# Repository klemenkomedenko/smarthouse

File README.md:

# smarthouse
smart house based on FPGA

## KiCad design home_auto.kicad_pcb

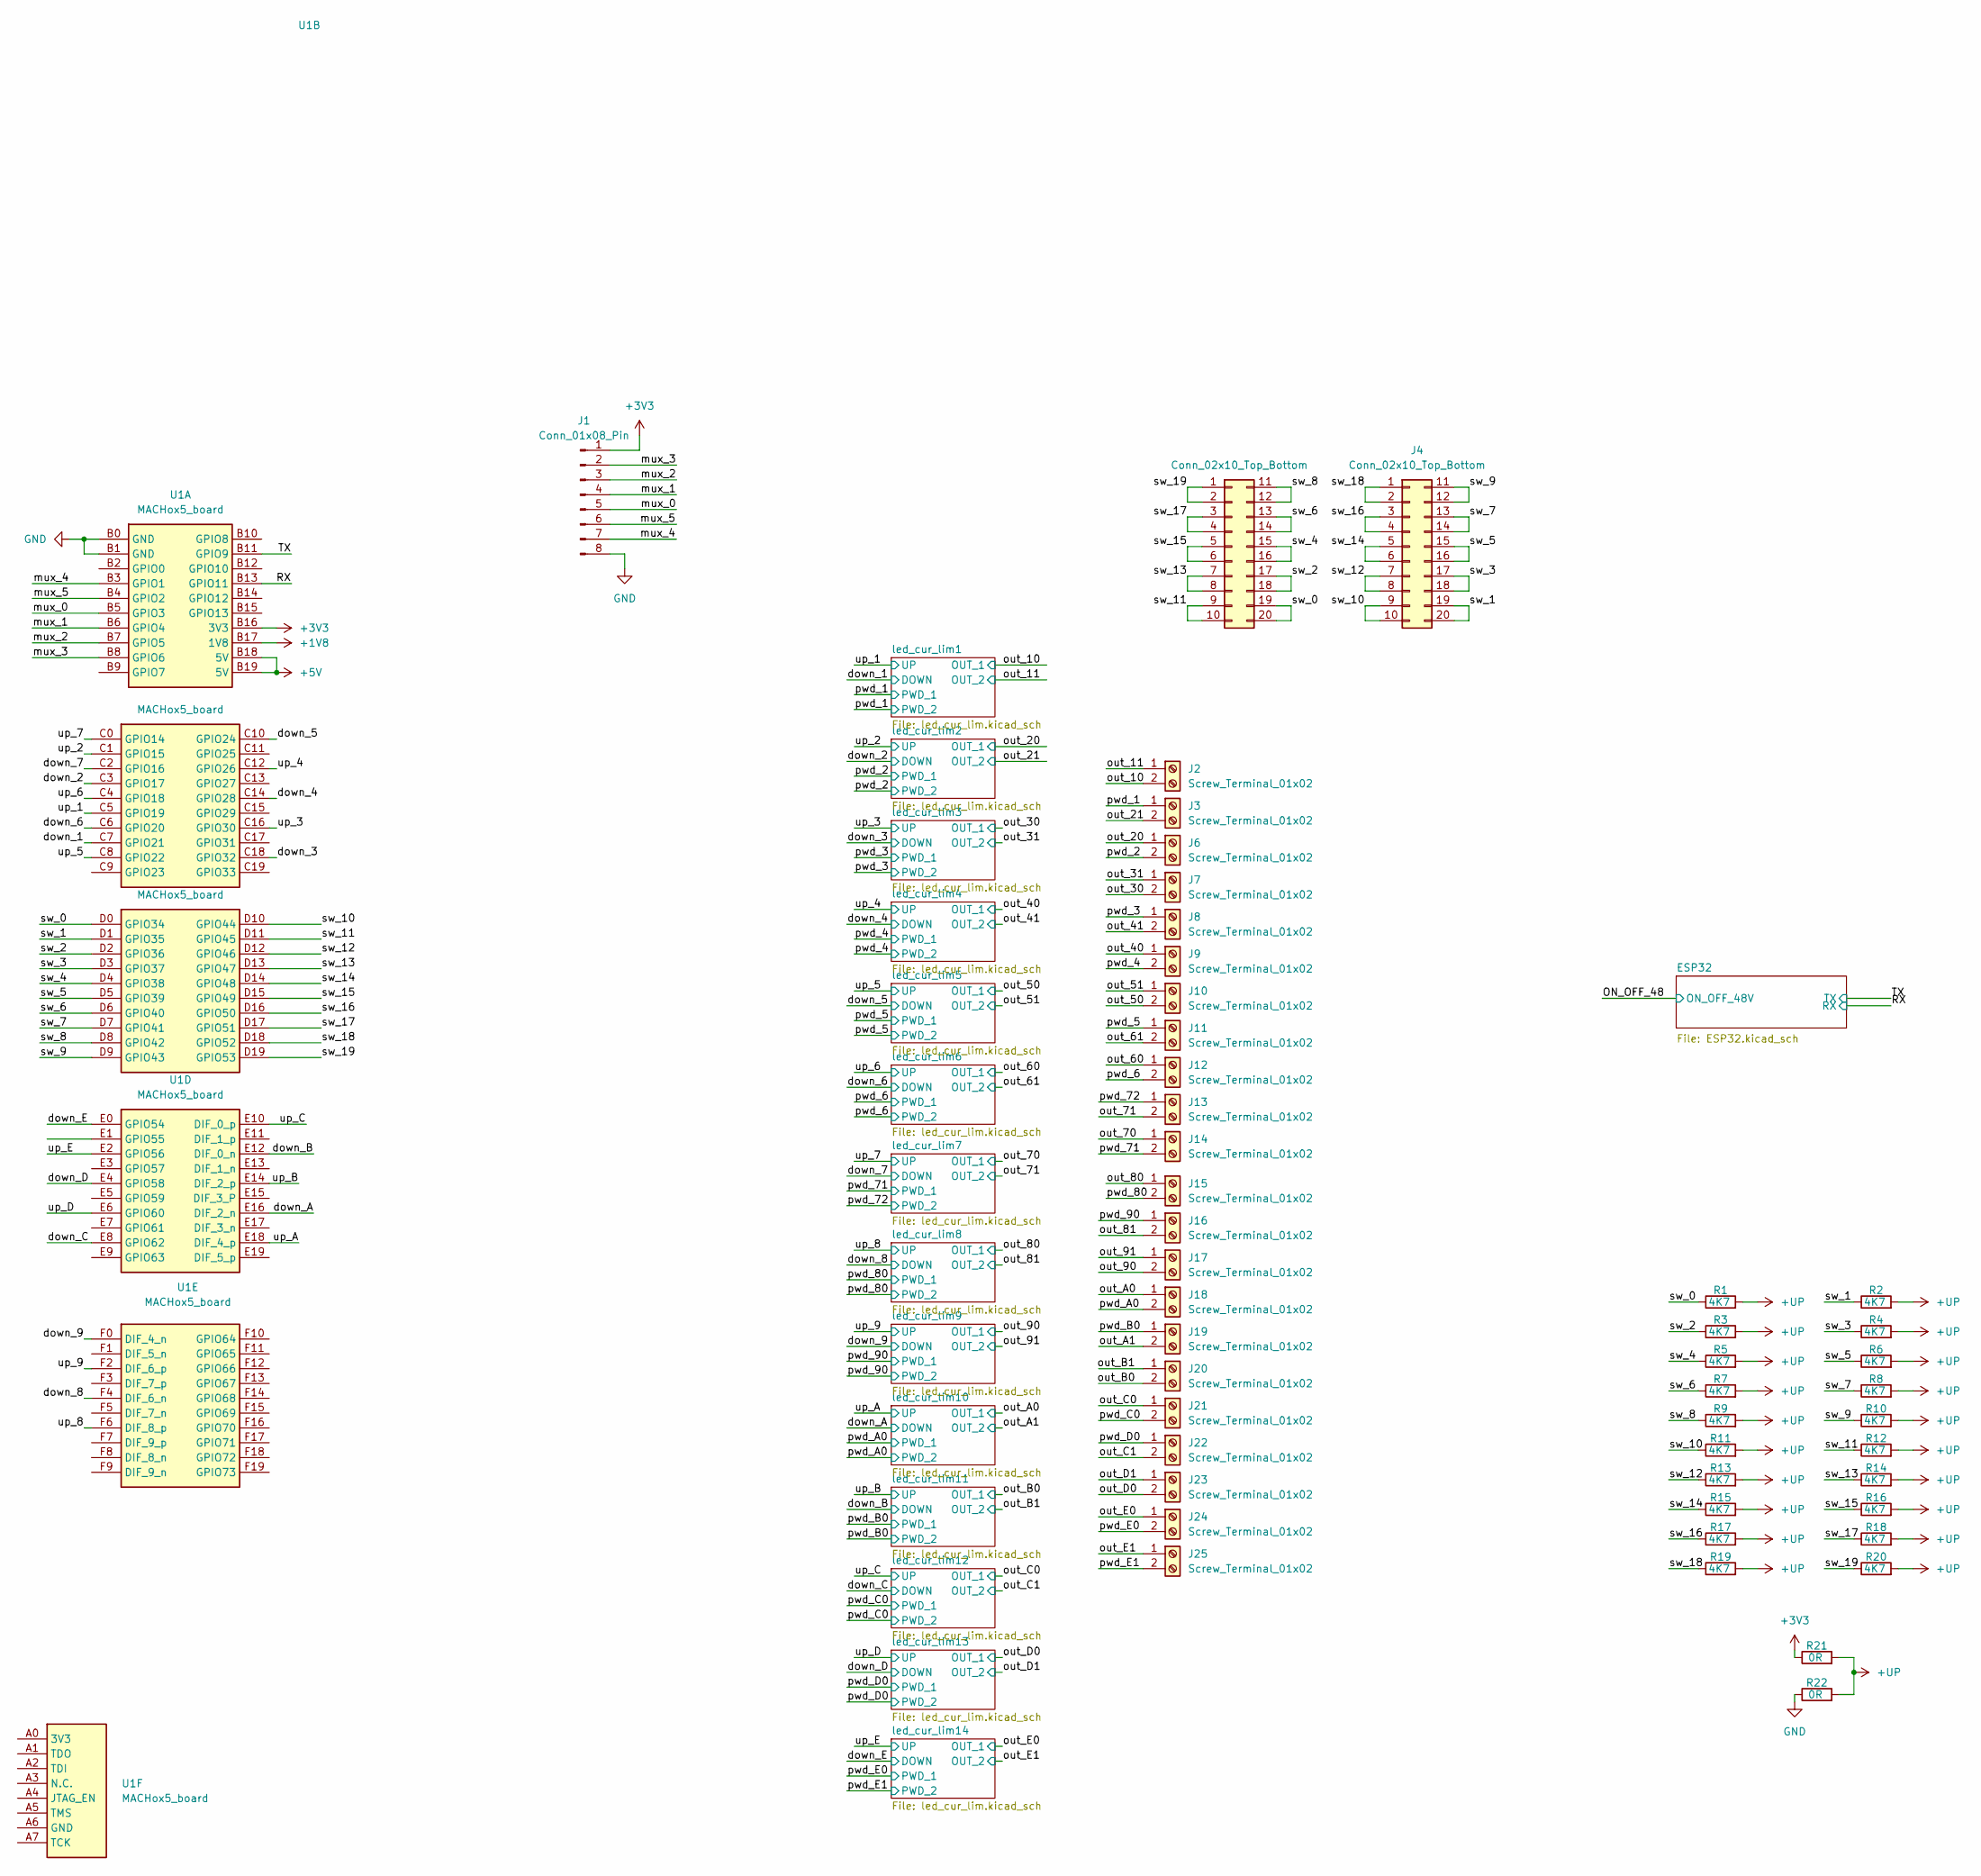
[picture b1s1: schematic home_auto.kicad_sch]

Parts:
J1: Conn_01x08_Pin; PinHeader_1x08_P2.54mm_Vertical
J2, J3, J6, J7, J8, J9, J10, J11, J12, J13, J14, J15, J16, J17, J18, J19, J20, J21, J22, J23, J24, J25: Screw_Terminal_01x02; TC0203620000G
J4, J5: Conn_02x10_Top_Bottom; PinHeader_2x10_P2.54mm_Vertical_SMD
R1, R2, R3, R4, R5, R6, R7, R8, R9, R10, R11, R12, R13, R14, R15, R16, R17, R18, R19, R20: 4K7; R_0603_1608Metric
R21: 0R; R_0805_2012Metric
R22: 0R; R_0603_1608Metric
U1: MACHox5_board; machox5_board

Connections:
+1V8: U1.B17 (1V8)
+3V3: J1.1, R21.1, U1.B16 (3V3); also elsewhere on the board
+5V: U1.B18 (5V), U1.B19 (5V); also elsewhere on the board
+UP: R1.2, R2.2, R3.2, R4.2, R5.2, R6.2, R7.2, R8.2, R9.2, R10.2, R11.2, R12.2, R13.2, R14.2, R15.2, R16.2, R17.2, R18.2, R19.2, R20.2, R21.2, R22.2
/RX: U1.B13 (GPIO11); also elsewhere on the board
/TX: U1.B11 (GPIO9); also elsewhere on the board
/down_1: U1.C7 (GPIO21); also elsewhere on the board
/down_2: U1.C3 (GPIO17); also elsewhere on the board
/down_3: U1.C18 (GPIO32); also elsewhere on the board
/down_4: U1.C14 (GPIO28); also elsewhere on the board
/down_5: U1.C10 (GPIO24); also elsewhere on the board
/down_6: U1.C6 (GPIO20); also elsewhere on the board
/down_7: U1.C2 (GPIO16); also elsewhere on the board
/down_8: U1.F4 (DIF_6_n); also elsewhere on the board
/down_9: U1.F0 (DIF_4_n); also elsewhere on the board
/down_A: U1.E16 (DIF_2_n); also elsewhere on the board
/down_B: U1.E12 (DIF_0_n); also elsewhere on the board
/down_C: U1.E8 (GPIO62); also elsewhere on the board
/down_D: U1.E4 (GPIO58); also elsewhere on the board
/down_E: U1.E0 (GPIO54); also elsewhere on the board
/mux_0: J1.5, U1.B5 (GPIO3)
/mux_1: J1.4, U1.B6 (GPIO4)
/mux_2: J1.3, U1.B7 (GPIO5)
/mux_3: J1.2, U1.B8 (GPIO6)
/mux_4: J1.7, U1.B3 (GPIO1)
/mux_5: J1.6, U1.B4 (GPIO2)
/out_10: J2.2; also elsewhere on the board
/out_11: J2.1; also elsewhere on the board
/out_20: J6.1; also elsewhere on the board
/out_21: J3.2; also elsewhere on the board
/out_30: J7.2; also elsewhere on the board
/out_31: J7.1; also elsewhere on the board
/out_40: J9.1; also elsewhere on the board
/out_41: J8.2; also elsewhere on the board
/out_50: J10.2; also elsewhere on the board
/out_51: J10.1; also elsewhere on the board
/out_60: J12.1; also elsewhere on the board
/out_61: J11.2; also elsewhere on the board
/out_70: J14.1; also elsewhere on the board
/out_71: J13.2; also elsewhere on the board
/out_80: J15.1; also elsewhere on the board
/out_81: J16.2; also elsewhere on the board
/out_90: J17.2; also elsewhere on the board
/out_91: J17.1; also elsewhere on the board
/out_A0: J18.1; also elsewhere on the board
/out_A1: J19.2; also elsewhere on the board
/out_B0: J20.2; also elsewhere on the board
/out_B1: J20.1; also elsewhere on the board
/out_C0: J21.1; also elsewhere on the board
/out_C1: J22.2; also elsewhere on the board
/out_D0: J23.2; also elsewhere on the board
/out_D1: J23.1; also elsewhere on the board
/out_E0: J24.1; also elsewhere on the board
/out_E1: J25.1; also elsewhere on the board
/pwd_1: J3.1; also elsewhere on the board
/pwd_2: J6.2; also elsewhere on the board
/pwd_3: J8.1; also elsewhere on the board
/pwd_4: J9.2; also elsewhere on the board
/pwd_5: J11.1; also elsewhere on the board
/pwd_6: J12.2; also elsewhere on the board
/pwd_71: J14.2; also elsewhere on the board
/pwd_72: J13.1; also elsewhere on the board
/pwd_80: J15.2; also elsewhere on the board
/pwd_90: J16.1; also elsewhere on the board
/pwd_A0: J18.2; also elsewhere on the board
/pwd_B0: J19.1; also elsewhere on the board
/pwd_C0: J21.2; also elsewhere on the board
/pwd_D0: J22.1; also elsewhere on the board
/pwd_E0: J24.2; also elsewhere on the board
/pwd_E1: J25.2; also elsewhere on the board
/sw_0: J5.19, J5.20, R1.1, U1.D0 (GPIO34)
/sw_1: J4.19, J4.20, R2.1, U1.D1 (GPIO35)
/sw_2: J5.17, J5.18, R3.1, U1.D2 (GPIO36)
/sw_3: J4.17, J4.18, R4.1, U1.D3 (GPIO37)
/sw_4: J5.15, J5.16, R5.1, U1.D4 (GPIO38)
/sw_5: J4.15, J4.16, R6.1, U1.D5 (GPIO39)
/sw_6: J5.13, J5.14, R7.1, U1.D6 (GPIO40)
/sw_7: J4.13, J4.14, R8.1, U1.D7 (GPIO41)
/sw_8: J5.11, J5.12, R9.1, U1.D8 (GPIO42)
/sw_9: J4.11, J4.12, R10.1, U1.D9 (GPIO43)
/sw_10: J4.9, J4.10, R11.1, U1.D10 (GPIO44)
/sw_11: J5.9, J5.10, R12.1, U1.D11 (GPIO45)
/sw_12: J4.7, J4.8, R13.1, U1.D12 (GPIO46)
/sw_13: J5.7, J5.8, R14.1, U1.D13 (GPIO47)
/sw_14: J4.5, J4.6, R15.1, U1.D14 (GPIO48)
/sw_15: J5.5, J5.6, R16.1, U1.D15 (GPIO49)
/sw_16: J4.3, J4.4, R17.1, U1.D16 (GPIO50)
/sw_17: J5.3, J5.4, R18.1, U1.D17 (GPIO51)
/sw_18: J4.1, J4.2, R19.1, U1.D18 (GPIO52)
/sw_19: J5.1, J5.2, R20.1, U1.D19 (GPIO53)
/up_1: U1.C5 (GPIO19); also elsewhere on the board
/up_2: U1.C1 (GPIO15); also elsewhere on the board
/up_3: U1.C16 (GPIO30); also elsewhere on the board
/up_4: U1.C12 (GPIO26); also elsewhere on the board
/up_5: U1.C8 (GPIO22); also elsewhere on the board
/up_6: U1.C4 (GPIO18); also elsewhere on the board
/up_7: U1.C0 (GPIO14); also elsewhere on the board
/up_8: U1.F6 (DIF_8_p); also elsewhere on the board
/up_9: U1.F2 (DIF_6_p); also elsewhere on the board
/up_A: U1.E18 (DIF_4_p); also elsewhere on the board
/up_B: U1.E14 (DIF_2_p); also elsewhere on the board
/up_C: U1.E10 (DIF_0_p); also elsewhere on the board
/up_D: U1.E6 (GPIO60); also elsewhere on the board
/up_E: U1.E2 (GPIO56); also elsewhere on the board
GND: J1.8, R22.1, U1.B0 (GND), U1.B1 (GND); also elsewhere on the board

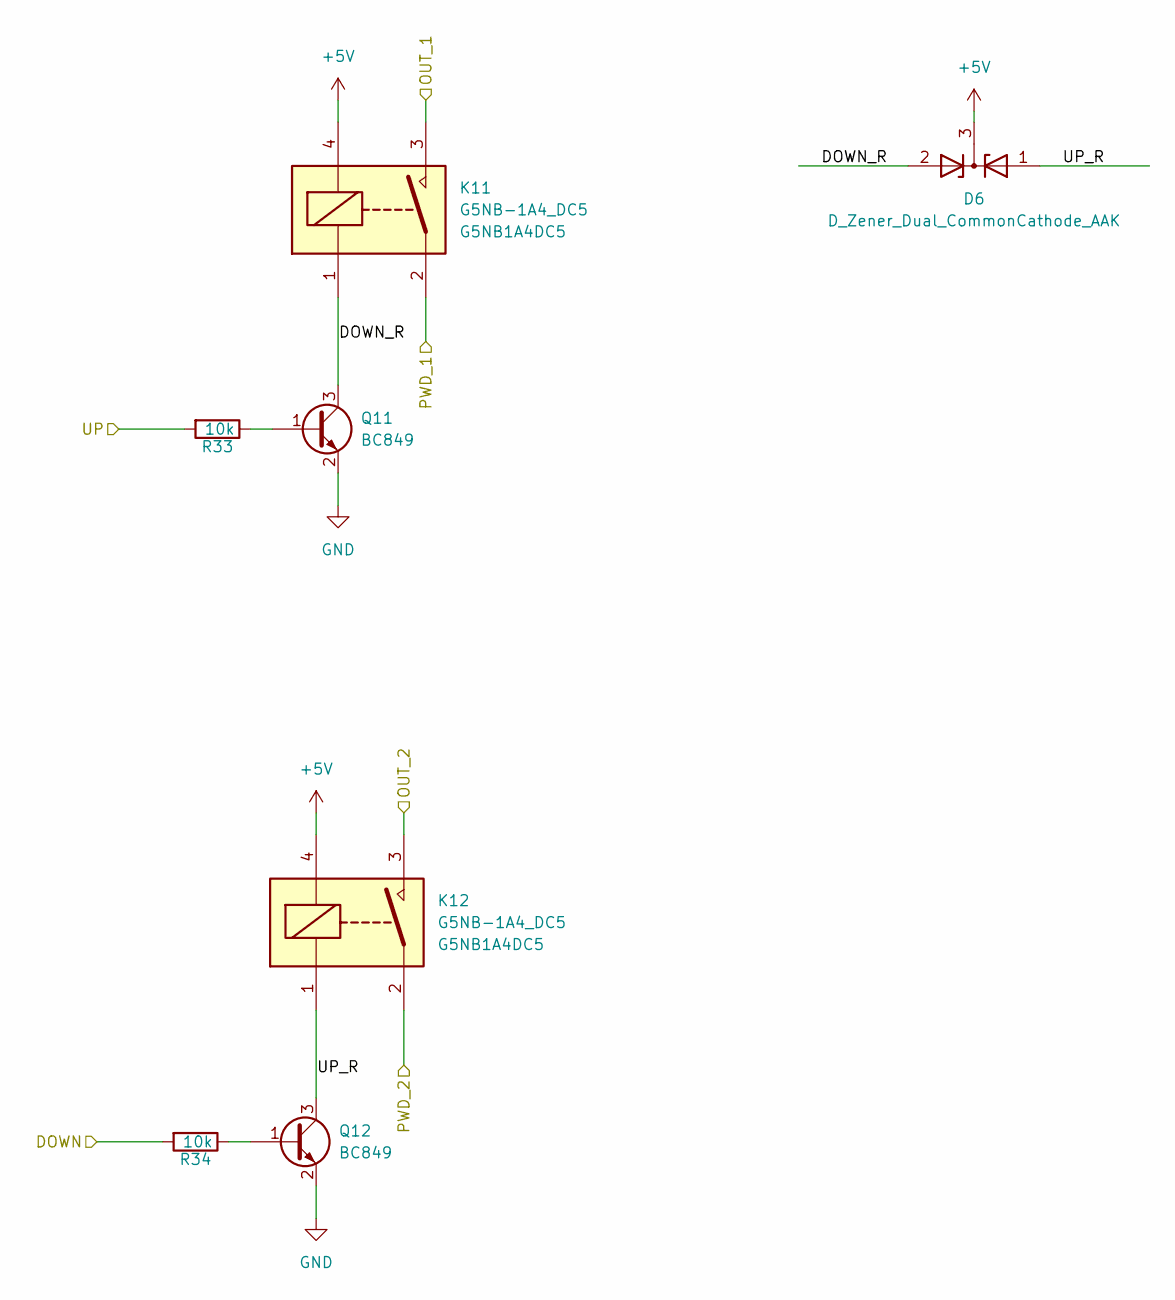
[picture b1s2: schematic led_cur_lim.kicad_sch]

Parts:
D6: D_Zener_Dual_CommonCathode_AAK; SOT-23
K11, K12: G5NB-1A4_DC5; G5NB1A4DC5; Mouser Part Number 653-G5NB-1A4DC5
Q11, Q12: BC849; SOT-23
R33, R34: 10k; R_0603_1608Metric

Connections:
+5V: D6.3 (K), K11.4, K12.4; also elsewhere on the board
/down_1: R34.2; also elsewhere on the board
/led_cur_lim1/DOWN_R: D6.2 (A), K11.1, Q11.3 (C)
/led_cur_lim1/UP_R: D6.1 (A), K12.1, Q12.3 (C)
/out_10: K11.3; also elsewhere on the board
/out_11: K12.3; also elsewhere on the board
/pwd_1: K11.2, K12.2; also elsewhere on the board
/up_1: R33.2; also elsewhere on the board
GND: Q11.2 (E), Q12.2 (E); also elsewhere on the board
unnamed: Q11.1 (B), R33.1
unnamed: Q12.1 (B), R34.1

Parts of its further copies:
D1, D2, D3, D4, D5, D7, D8, D9, D10, D11, D12, D13, D14: D_Zener_Dual_CommonCathode_AAK; SOT-23
K1, K2, K3, K4, K5, K6, K7, K8, K9, K10, K13, K14, K15, K16, K17, K18, K19, K20, K21, K22, K23, K24, K25, K26, K27, K28: G5NB-1A4_DC5; G5NB1A4DC5; Mouser Part Number 653-G5NB-1A4DC5
Q1, Q2, Q3, Q4, Q5, Q6, Q7, Q8, Q9, Q10, Q13, Q14, Q15, Q16, Q17, Q18, Q19, Q20, Q21, Q22, Q23, Q24, Q25, Q26, Q27, Q28: BC849; SOT-23
R23, R24, R25, R26, R27, R28, R29, R30, R31, R32, R35, R36, R37, R38, R39, R40, R41, R42, R43, R44, R45, R46, R47, R48, R49, R50: 10k; R_0603_1608Metric

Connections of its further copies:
+5V: D1.3 (K), D2.3 (K), D3.3 (K), D4.3 (K), D5.3 (K), D7.3 (K), D8.3 (K), D9.3 (K), D10.3 (K), D11.3 (K), D12.3 (K), D13.3 (K), D14.3 (K), K1.4, K2.4, K3.4, K4.4, K5.4, K6.4, K7.4, K8.4, K9.4, K10.4, K13.4, K14.4, K15.4, K16.4, K17.4, K18.4, K19.4, K20.4, K21.4, K22.4, K23.4, K24.4, K25.4, K26.4, K27.4, K28.4; also elsewhere on the board
/down_2: R24.2; also elsewhere on the board
/down_3: R26.2; also elsewhere on the board
/down_4: R28.2; also elsewhere on the board
/down_5: R30.2; also elsewhere on the board
/down_6: R32.2; also elsewhere on the board
/down_7: R36.2; also elsewhere on the board
/down_8: R38.2; also elsewhere on the board
/down_9: R40.2; also elsewhere on the board
/down_A: R42.2; also elsewhere on the board
/down_B: R44.2; also elsewhere on the board
/down_C: R46.2; also elsewhere on the board
/down_D: R48.2; also elsewhere on the board
/down_E: R50.2; also elsewhere on the board
/led_cur_lim2/DOWN_R: D1.2 (A), K1.1, Q1.3 (C)
/led_cur_lim2/UP_R: D1.1 (A), K2.1, Q2.3 (C)
/led_cur_lim3/DOWN_R: D2.2 (A), K3.1, Q3.3 (C)
/led_cur_lim3/UP_R: D2.1 (A), K4.1, Q4.3 (C)
/led_cur_lim4/DOWN_R: D3.2 (A), K5.1, Q5.3 (C)
/led_cur_lim4/UP_R: D3.1 (A), K6.1, Q6.3 (C)
/led_cur_lim5/DOWN_R: D4.2 (A), K7.1, Q7.3 (C)
/led_cur_lim5/UP_R: D4.1 (A), K8.1, Q8.3 (C)
/led_cur_lim6/DOWN_R: D5.2 (A), K9.1, Q9.3 (C)
/led_cur_lim6/UP_R: D5.1 (A), K10.1, Q10.3 (C)
/led_cur_lim7/DOWN_R: D7.2 (A), K13.1, Q13.3 (C)
/led_cur_lim7/UP_R: D7.1 (A), K14.1, Q14.3 (C)
/led_cur_lim8/DOWN_R: D8.2 (A), K15.1, Q15.3 (C)
/led_cur_lim8/UP_R: D8.1 (A), K16.1, Q16.3 (C)
/led_cur_lim9/DOWN_R: D9.2 (A), K17.1, Q17.3 (C)
/led_cur_lim9/UP_R: D9.1 (A), K18.1, Q18.3 (C)
/led_cur_lim10/DOWN_R: D10.2 (A), K19.1, Q19.3 (C)
/led_cur_lim10/UP_R: D10.1 (A), K20.1, Q20.3 (C)
/led_cur_lim11/DOWN_R: D11.2 (A), K21.1, Q21.3 (C)
/led_cur_lim11/UP_R: D11.1 (A), K22.1, Q22.3 (C)
/led_cur_lim12/DOWN_R: D12.2 (A), K23.1, Q23.3 (C)
/led_cur_lim12/UP_R: D12.1 (A), K24.1, Q24.3 (C)
/led_cur_lim13/DOWN_R: D13.2 (A), K25.1, Q25.3 (C)
/led_cur_lim13/UP_R: D13.1 (A), K26.1, Q26.3 (C)
/led_cur_lim14/DOWN_R: D14.2 (A), K27.1, Q27.3 (C)
/led_cur_lim14/UP_R: D14.1 (A), K28.1, Q28.3 (C)
/out_20: K1.3; also elsewhere on the board
/out_21: K2.3; also elsewhere on the board
/out_30: K3.3; also elsewhere on the board
/out_31: K4.3; also elsewhere on the board
/out_40: K5.3; also elsewhere on the board
/out_41: K6.3; also elsewhere on the board
/out_50: K7.3; also elsewhere on the board
/out_51: K8.3; also elsewhere on the board
/out_60: K9.3; also elsewhere on the board
/out_61: K10.3; also elsewhere on the board
/out_70: K13.3; also elsewhere on the board
/out_71: K14.3; also elsewhere on the board
/out_80: K15.3; also elsewhere on the board
/out_81: K16.3; also elsewhere on the board
/out_90: K17.3; also elsewhere on the board
/out_91: K18.3; also elsewhere on the board
/out_A0: K19.3; also elsewhere on the board
/out_A1: K20.3; also elsewhere on the board
/out_B0: K21.3; also elsewhere on the board
/out_B1: K22.3; also elsewhere on the board
/out_C0: K23.3; also elsewhere on the board
/out_C1: K24.3; also elsewhere on the board
/out_D0: K25.3; also elsewhere on the board
/out_D1: K26.3; also elsewhere on the board
/out_E0: K27.3; also elsewhere on the board
/out_E1: K28.3; also elsewhere on the board
/pwd_2: K1.2, K2.2; also elsewhere on the board
/pwd_3: K3.2, K4.2; also elsewhere on the board
/pwd_4: K5.2, K6.2; also elsewhere on the board
/pwd_5: K7.2, K8.2; also elsewhere on the board
/pwd_6: K9.2, K10.2; also elsewhere on the board
/pwd_71: K13.2; also elsewhere on the board
/pwd_72: K14.2; also elsewhere on the board
/pwd_80: K15.2, K16.2; also elsewhere on the board
/pwd_90: K17.2, K18.2; also elsewhere on the board
/pwd_A0: K19.2, K20.2; also elsewhere on the board
/pwd_B0: K21.2, K22.2; also elsewhere on the board
/pwd_C0: K23.2, K24.2; also elsewhere on the board
/pwd_D0: K25.2, K26.2; also elsewhere on the board
/pwd_E0: K27.2; also elsewhere on the board
/pwd_E1: K28.2; also elsewhere on the board
/up_2: R23.2; also elsewhere on the board
/up_3: R25.2; also elsewhere on the board
/up_4: R27.2; also elsewhere on the board
/up_5: R29.2; also elsewhere on the board
/up_6: R31.2; also elsewhere on the board
/up_7: R35.2; also elsewhere on the board
/up_8: R37.2; also elsewhere on the board
/up_9: R39.2; also elsewhere on the board
/up_A: R41.2; also elsewhere on the board
/up_B: R43.2; also elsewhere on the board
/up_C: R45.2; also elsewhere on the board
/up_D: R47.2; also elsewhere on the board
/up_E: R49.2; also elsewhere on the board
GND: Q1.2 (E), Q2.2 (E), Q3.2 (E), Q4.2 (E), Q5.2 (E), Q6.2 (E), Q7.2 (E), Q8.2 (E), Q9.2 (E), Q10.2 (E), Q13.2 (E), Q14.2 (E), Q15.2 (E), Q16.2 (E), Q17.2 (E), Q18.2 (E), Q19.2 (E), Q20.2 (E), Q21.2 (E), Q22.2 (E), Q23.2 (E), Q24.2 (E), Q25.2 (E), Q26.2 (E), Q27.2 (E), Q28.2 (E); also elsewhere on the board
unnamed: Q1.1 (B), R23.1
unnamed: Q2.1 (B), R24.1
unnamed: Q3.1 (B), R25.1
unnamed: Q4.1 (B), R26.1
unnamed: Q5.1 (B), R27.1
unnamed: Q6.1 (B), R28.1
unnamed: Q7.1 (B), R29.1
unnamed: Q8.1 (B), R30.1
unnamed: Q9.1 (B), R31.1
unnamed: Q10.1 (B), R32.1
unnamed: Q13.1 (B), R35.1
unnamed: Q14.1 (B), R36.1
unnamed: Q15.1 (B), R37.1
unnamed: Q16.1 (B), R38.1
unnamed: Q17.1 (B), R39.1
unnamed: Q18.1 (B), R40.1
unnamed: Q19.1 (B), R41.1
unnamed: Q20.1 (B), R42.1
unnamed: Q21.1 (B), R43.1
unnamed: Q22.1 (B), R44.1
unnamed: Q23.1 (B), R45.1
unnamed: Q24.1 (B), R46.1
unnamed: Q25.1 (B), R47.1
unnamed: Q26.1 (B), R48.1
unnamed: Q27.1 (B), R49.1
unnamed: Q28.1 (B), R50.1

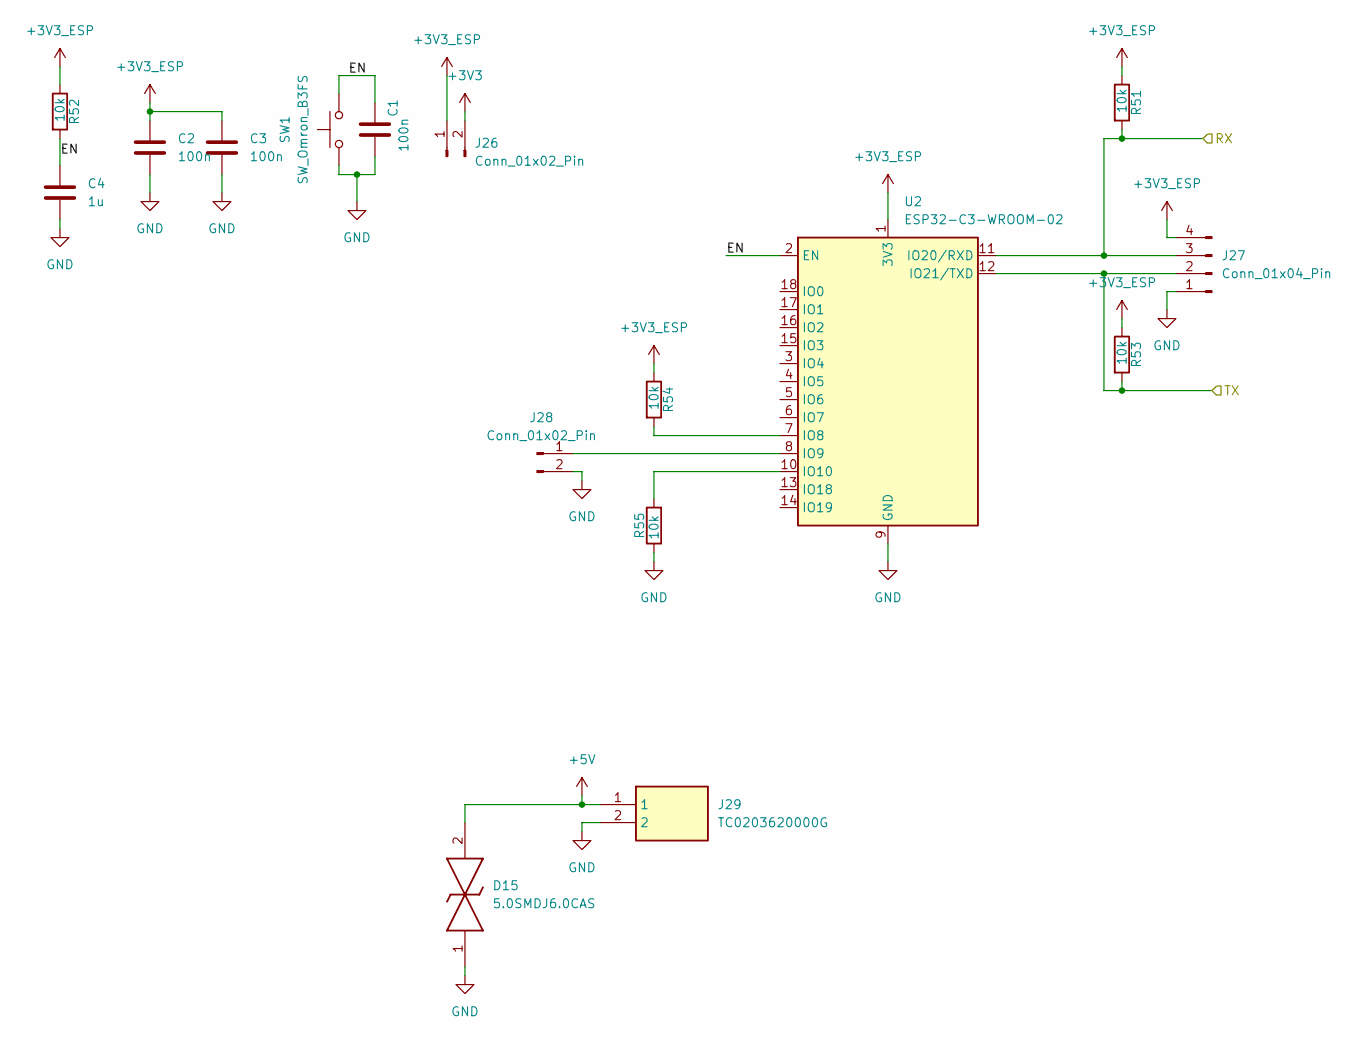
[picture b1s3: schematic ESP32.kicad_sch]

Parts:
C1, C2, C3: 100n; C_0603_1608Metric
C4: 1u; C_0603_1608Metric
D15: 5.0SMDJ6.0CAS; DIONM7959X262N; Mouser Part Number 576-5.0SMDJ6.0CAS
J26, J28: Conn_01x02_Pin; PinHeader_1x02_P1.27mm_Vertical
J27: Conn_01x04_Pin; PinHeader_1x04_P2.54mm_Vertical
J29: TC0203620000G; Mouser Part Number 649-TC02036200J0G
R51, R52, R53, R54, R55: 10k; R_0603_1608Metric
SW1: SW_Omron_B3FS; SW_SPST_Omron_B3FS-105xP
U2: ESP32-C3-WROOM-02

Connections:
+3V3: J26.2; also elsewhere on the board
+3V3_ESP: C2.1, C3.1, J26.1, J27.4, R51.1, R52.1, R53.1, R54.1, U2.1 (3V3)
+5V: D15.2, J29.1; also elsewhere on the board
/ESP32/EN: C1.1, C4.1, R52.2, SW1.2, U2.2 (EN)
/RX: J27.3, R51.2, U2.11 (IO20/RXD); also elsewhere on the board
/TX: J27.2, R53.2, U2.12 (IO21/TXD); also elsewhere on the board
GND: C1.2, C2.2, C3.2, C4.2, D15.1, J27.1, J28.2, J29.2, R55.1, SW1.1, U2.9 (GND), U2.19 (GND); also elsewhere on the board
unnamed: J28.1, U2.8 (IO9)
unnamed: R54.2, U2.7 (IO8)
unnamed: R55.2, U2.10 (IO10)

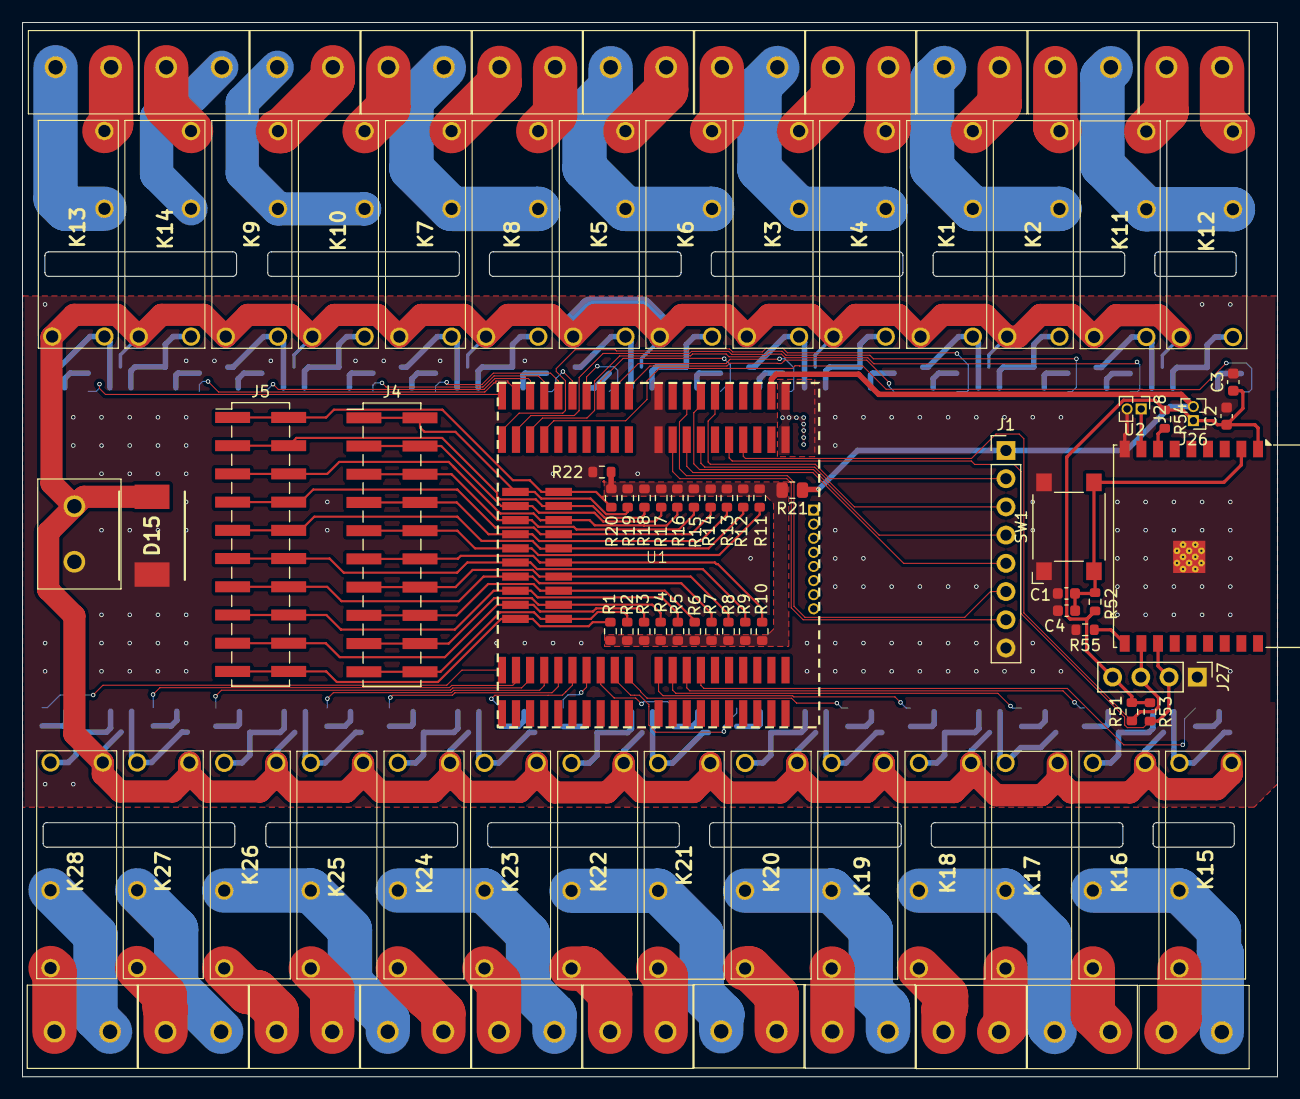
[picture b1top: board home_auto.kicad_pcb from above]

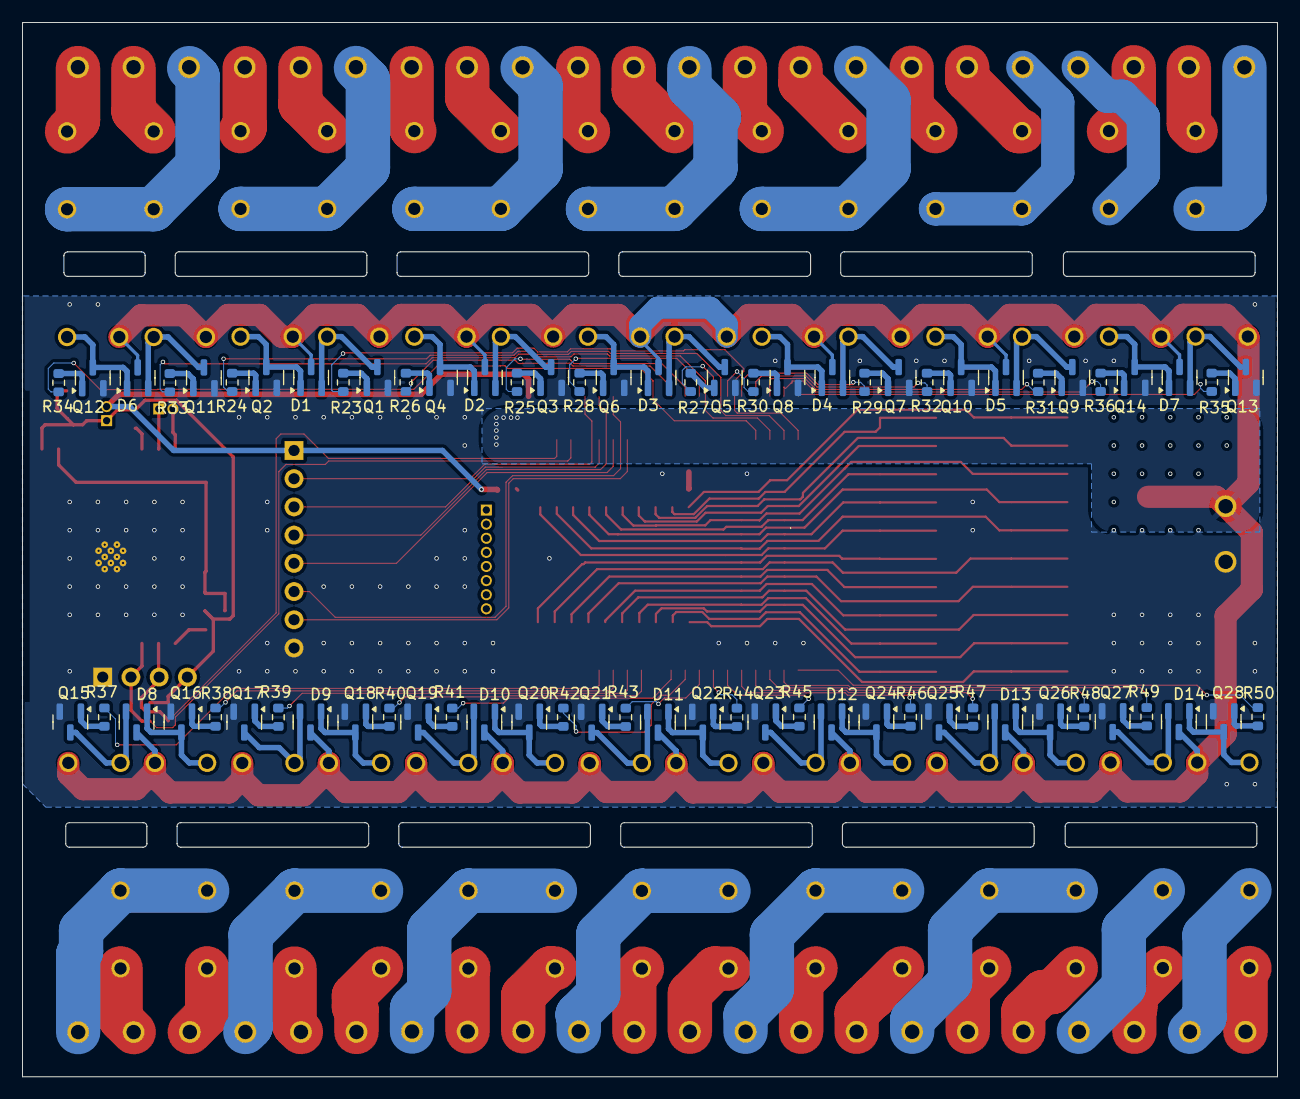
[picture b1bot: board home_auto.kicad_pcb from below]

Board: 2 copper layers, 113.0 x 94.9 mm, 162 parts (70 on the bottom side), 165 nets.

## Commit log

2024-11-05 board with normal header pins
2024-11-05 relay unit
2024-11-06 relay placment
2024-11-10 filse fo JCL pcb generated
2024-11-10 zip file
2024-11-10 fix layout
